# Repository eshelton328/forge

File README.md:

# forge

Hardware design monorepo for KiCad PCB projects with automated CI/CD.

Repository: [eshelton328/forge](https://github.com/eshelton328/forge).

For the alarm product, start with the [Rooster engineering map](projects/rooster/README.md).
Agent guidance is in [AGENTS.md](AGENTS.md). The [October 4 audit](docs/audits/2026-10-04-forge-rooster.md)
covers source consolidation, hardware readiness, costs and the development workflow.

## Repository Structure

```
forge/
├── Makefile          # make check / erc / drc / fab-drc
├── boards/           # Individual board projects
├── designs/          # Schematic studies before PCB layout
├── enclosures/       # Product packaging, Blender models and fit evidence
├── fab-rules/        # DRC rule templates per fab house
├── firmware/rooster/ # Reserved application, diagnostics and shared-code paths
├── kibot/            # KiBot output generation configs
├── libs/             # Shared libraries (symbols, footprints, 3D models)
├── projects/rooster/ # Product entry point and source manifest
├── releases/rooster/ # Release conventions; no product release declared
├── scripts/          # Automation scripts
├── emi/              # openEMS + gerber2ems (FDTD / EMI-adjacent smoke; see emi/README.md)
└── .github/workflows # CI/CD pipelines
```

## Boards

<!-- board-catalog-start -->
| Board | Description | Layers |
|---|---|---:|
| [alec-controls](boards/alec-controls/README.md) | ALEC bottom controls with three settings buttons and hardware enable switch | 2 |
| [alec-front](boards/alec-front/README.md) | ALEC exterior battery-check button and RGB LED | 2 |
| [alec-main](boards/alec-main/README.md) | ALEC main board with ESP32-S3, dual TPS63070 rails, audio and remote controls | 4 |
| [alec-sensor](boards/alec-sensor/README.md) | ALEC shower presence sensor prototype with ESP32-S3, RV-3028, isolated LD2410C and dual TPS63070 rails | 4 |
| [esp32s3-devkit](boards/esp32s3-devkit/README.md) | ESP32-S3-WROOM-1 development board with TPS63070 buck-boost and USB-C | 4 |
| [esp32s3-devkit-5v](boards/esp32s3-devkit-5v/README.md) | ESP32-S3-WROOM-1 dev board with dual TPS63070 rails (3.3V + 5V), USB-C | 4 |
| [tps63070-breakout](boards/tps63070-breakout/README.md) | TPS63070 3.3V buck-boost breakout board | 2 |
<!-- board-catalog-end -->

Each board README includes schematic previews, a downloadable schematic PDF, top/bottom 3D renders and a populated GLB model. The board catalog and these assets are updated automatically after merges to `main`.

The **ALEC** alarm uses `alec-main`, `alec-controls` and `alec-front` together. The main board carries the ESP32-S3, dual power converters and audio circuit; the two smaller boards carry the protected settings controls and exterior battery-check button/RGB LED. These are engineering prototypes with physical qualification pending. See the [full PCB and enclosure test report](boards/alec-main/review/TEST-REPORT.md).

The separate [ALEC Sensor](boards/alec-sensor/) is the shower presence companion: a routed four-layer PCB with LD2410C radar, RTC wake and isolated sensor signals. Its [S1 report](boards/alec-sensor/TEST-REPORT.md) covers electrical checks, free-tool power screening and nominal enclosure fit. Scheduled sensing is the proposed battery-saving default; waterproofing and wet detection still require prototypes.

## Enclosures

| Enclosure | Board | Status |
|---|---|---|
| [ALEC v4.2](enclosures/alec/pcb-revision/) | alec-main, alec-controls, alec-front | Integrated PCB prototype: 105 mm cube, four perforated walls, 1.3-inch OLED and three AA cells; physical tests pending |
| [ALEC Sensor S1.1](enclosures/alec-sensor/) | alec-sensor | Circular 116 mm × 54 mm fit prototype with rear-access cells/controls, actual PCB and LD2410C; RF, sealing and thermal tests pending |
| [ALEC v4.1 reference](enclosures/alec/) | esp32s3-devkit-5v | Earlier packaging reference with the bench board |

The enclosure project includes editable Blender scenes, inline preview images, dimensional sources, a parts register and a reproducible test report. Open its README to download the models and review the current fit limits.

## CI/CD Pipeline

Every pull request automatically runs:
- **PR title** must follow [Conventional Commits](https://www.conventionalcommits.org/) (e.g. `feat:`, `fix:`, `chore:`, `ci:`)
- **`pytest`** on `tests/` (Python **3.12**; see [`.github/workflows/pytest.yml`](.github/workflows/pytest.yml) — Spice integration cases skip unless `ngspice`/Docker exist)
- **Open-source EMS (openEMS + gerber2ems)** — optional path-filtered workflow ([`.github/workflows/emi-checks.yml`](.github/workflows/emi-checks.yml)): builds pinned **openEMS** + **gerber2ems** and runs an upstream example slice ([`emi/README.md`](emi/README.md)); not every PR
- **ERC** (Electrical Rules Check) on schematics
- **DRC** (Design Rules Check) against multiple fab house rules (JLCPCB, PCBWay)

The KiCad workflow always runs, but it only **executes** ERC/DRC for boards that are in scope: changes under `boards/<name>/` check only those boards, while changes to `libs/`, `fab-rules/`, `kibot/`, `scripts/`, the root `Makefile`, or `.github/workflows/pr-checks.yml` trigger checks on all boards. Doc-only diffs (e.g. just `README.md`) skip the heavy KiCad jobs to save time. **`pytest`** (see **`pytest.yml`**) runs on every PR regardless, so Python regressions cannot slip through doc-only merges.

The manually dispatched [fabrication workflow](.github/workflows/release.yml) generates files for a selected board; it does not currently run on release tags. Its outputs include:
- Fab-ready Gerber/drill ZIPs per fab house
- BOM and component placement files
- Schematic PDFs and board renders

These exports are not an approved Rooster manufacturing release. The product's
reviewed supplier packages and remaining assembly work are tracked separately;
see the [Rooster map](projects/rooster/README.md).

## Local Development

### Prerequisites

```bash
brew install --cask kicad    # KiCad 10 (includes kicad-cli)
pip install kibot kikit       # Automation tools
```

### Running checks locally

From the repository root, the **Makefile** is the usual entry point. **Each command checks one board** — the one named by `BOARD` (default: `esp32s3-devkit`). Nothing scans every board unless you ask for that explicitly.

```bash
make help           # list targets
make list-boards    # show board folder names you can pass as BOARD=...

# Default single board (esp32s3-devkit)
make check
make drc

# A different board — either form (folder and .kicad_* basename must match)
make drc BOARD=other-board
make drc other-board
make check other-board

# Optional: run make check for every board under boards/ (e.g. before a release)
make check-all
```

`kicad-cli` is picked up from your `PATH` if present; on macOS it falls back to
`/Applications/KiCad/KiCad.app/Contents/MacOS/kicad-cli`. Override with
`KICAD_CLI=/path/to/kicad-cli make check`.

### Python tests (pytest)

```bash
pip install -r requirements.txt
python3 -m pytest tests/
```

With **`ngspice`** and **Docker** available, `tests/test_spice_run_sim_integration.py` runs end-to-end Spice smoke; otherwise those cases are **skipped** (same as default CI for `pytest.yml`).

**SPICE / simulation (boards with `sim.yml`):** CI builds [`sim/docker/Dockerfile`](sim/docker/Dockerfile) — same KiCad digest as ERC/DRC plus pinned **ngspice** and the repo **`requirements.txt`** — and runs export + `run_sim.py` inside that image ([`sim/README.md`](sim/README.md)). Local parity: **`make sim-board-docker BOARD=tps63070-breakout`** or **`scripts/sim/run-spice-in-docker.sh --board …`**.

Raw commands (equivalent to the Makefile):

```bash
kicad-cli sch erc --exit-code-violations --format json -o boards/esp32s3-devkit/erc.json \
  boards/esp32s3-devkit/esp32s3-devkit.kicad_sch

kicad-cli pcb drc --exit-code-violations --refill-zones --schematic-parity --format json \
  -o boards/esp32s3-devkit/drc-default.json boards/esp32s3-devkit/esp32s3-devkit.kicad_pcb

./scripts/run-drc-all-fabs.sh boards/esp32s3-devkit
```

### Adding a new board

1. Create a new directory under `boards/`
2. Add a `board.yml` with layer count and fab targets
3. If using shared libraries, create project-local `fp-lib-table` / `sym-lib-table` pointing to `../../libs/`
4. Generate the initial schematic and model downloads with `bash scripts/ci/generate-board-images.sh boards/<name>` (`kicad-cli` must be on `PATH`), then run `python3 scripts/ci/update-board-readmes.py` to refresh the gallery and root catalog. Commit the generated `docs/` assets with the board.
5. Push a PR -- CI will automatically run checks; merge automation refreshes the galleries and catalog again.

## Fab House Rules

DRC rules for each fab house are stored in `fab-rules/` as `.kicad_dru` files. CI swaps these in and runs DRC to tell you which fabs your design is compatible with.

2-layer and 4-layer rules each come in two tiers where noted: **standard** (baseline process) vs **advanced** (tighter vias/clearances, typically higher cost). Each board declares which rule keys it runs in `board.yml`.

| Fab House | Rule File | Notes |
|-----------|-----------|-------|
| JLCPCB 2L Standard | `jlcpcb-2layer-standard.kicad_dru` | 0.3mm via drill, 0.15mm annular ring |
| JLCPCB 2L Advanced | `jlcpcb-2layer-advanced.kicad_dru` | 0.2mm via drill, 0.1mm annular ring |
| JLCPCB 4L Standard | `jlcpcb-4layer.kicad_dru` | |
| JLCPCB 4L Advanced | `jlcpcb-4layer-advanced.kicad_dru` | Tighter annular / hole clearance / pad-track clearance vs standard 4L |
| PCBWay 2L Standard | `pcbway-2layer-standard.kicad_dru` | 0.3mm via drill, 0.45mm via pad |
| PCBWay 2L Advanced | `pcbway-2layer-advanced.kicad_dru` | 0.2mm via drill, 0.35mm via pad |
| PCBWay 4L Standard | `pcbway-4layer.kicad_dru` | |
| PCBWay 4L Advanced | `pcbway-4layer-advanced.kicad_dru` | 0.2mm via drill, 0.35mm via pad vs standard 4L |

## Naming compatibility

The repository and checkout directory are named `forge`. The local and CI Docker
images use `forge-sim` and `forge-open-ems`.

A few references intentionally retain the previous name:

- The GitHub environment `the-forge` holds `FORGE_PAT`, used by the README publishing
  workflow. Keep the workflow attached to it until the secret is migrated.
- `scripts/alarm/design.py` uses `the-forge/alec/` as a deterministic UUID namespace.
  Changing it would regenerate KiCad component, pin and wire IDs.
- Recorded simulation reports, exported netlists and test transcripts retain the
  image names and paths used when they were produced. The physics report and its
  `scripts/physics/render_report.py` renderer retain their original GitHub link;
  the renderer is covered by the archived verification source hashes. Update these
  records through their normal regeneration and verification workflows.

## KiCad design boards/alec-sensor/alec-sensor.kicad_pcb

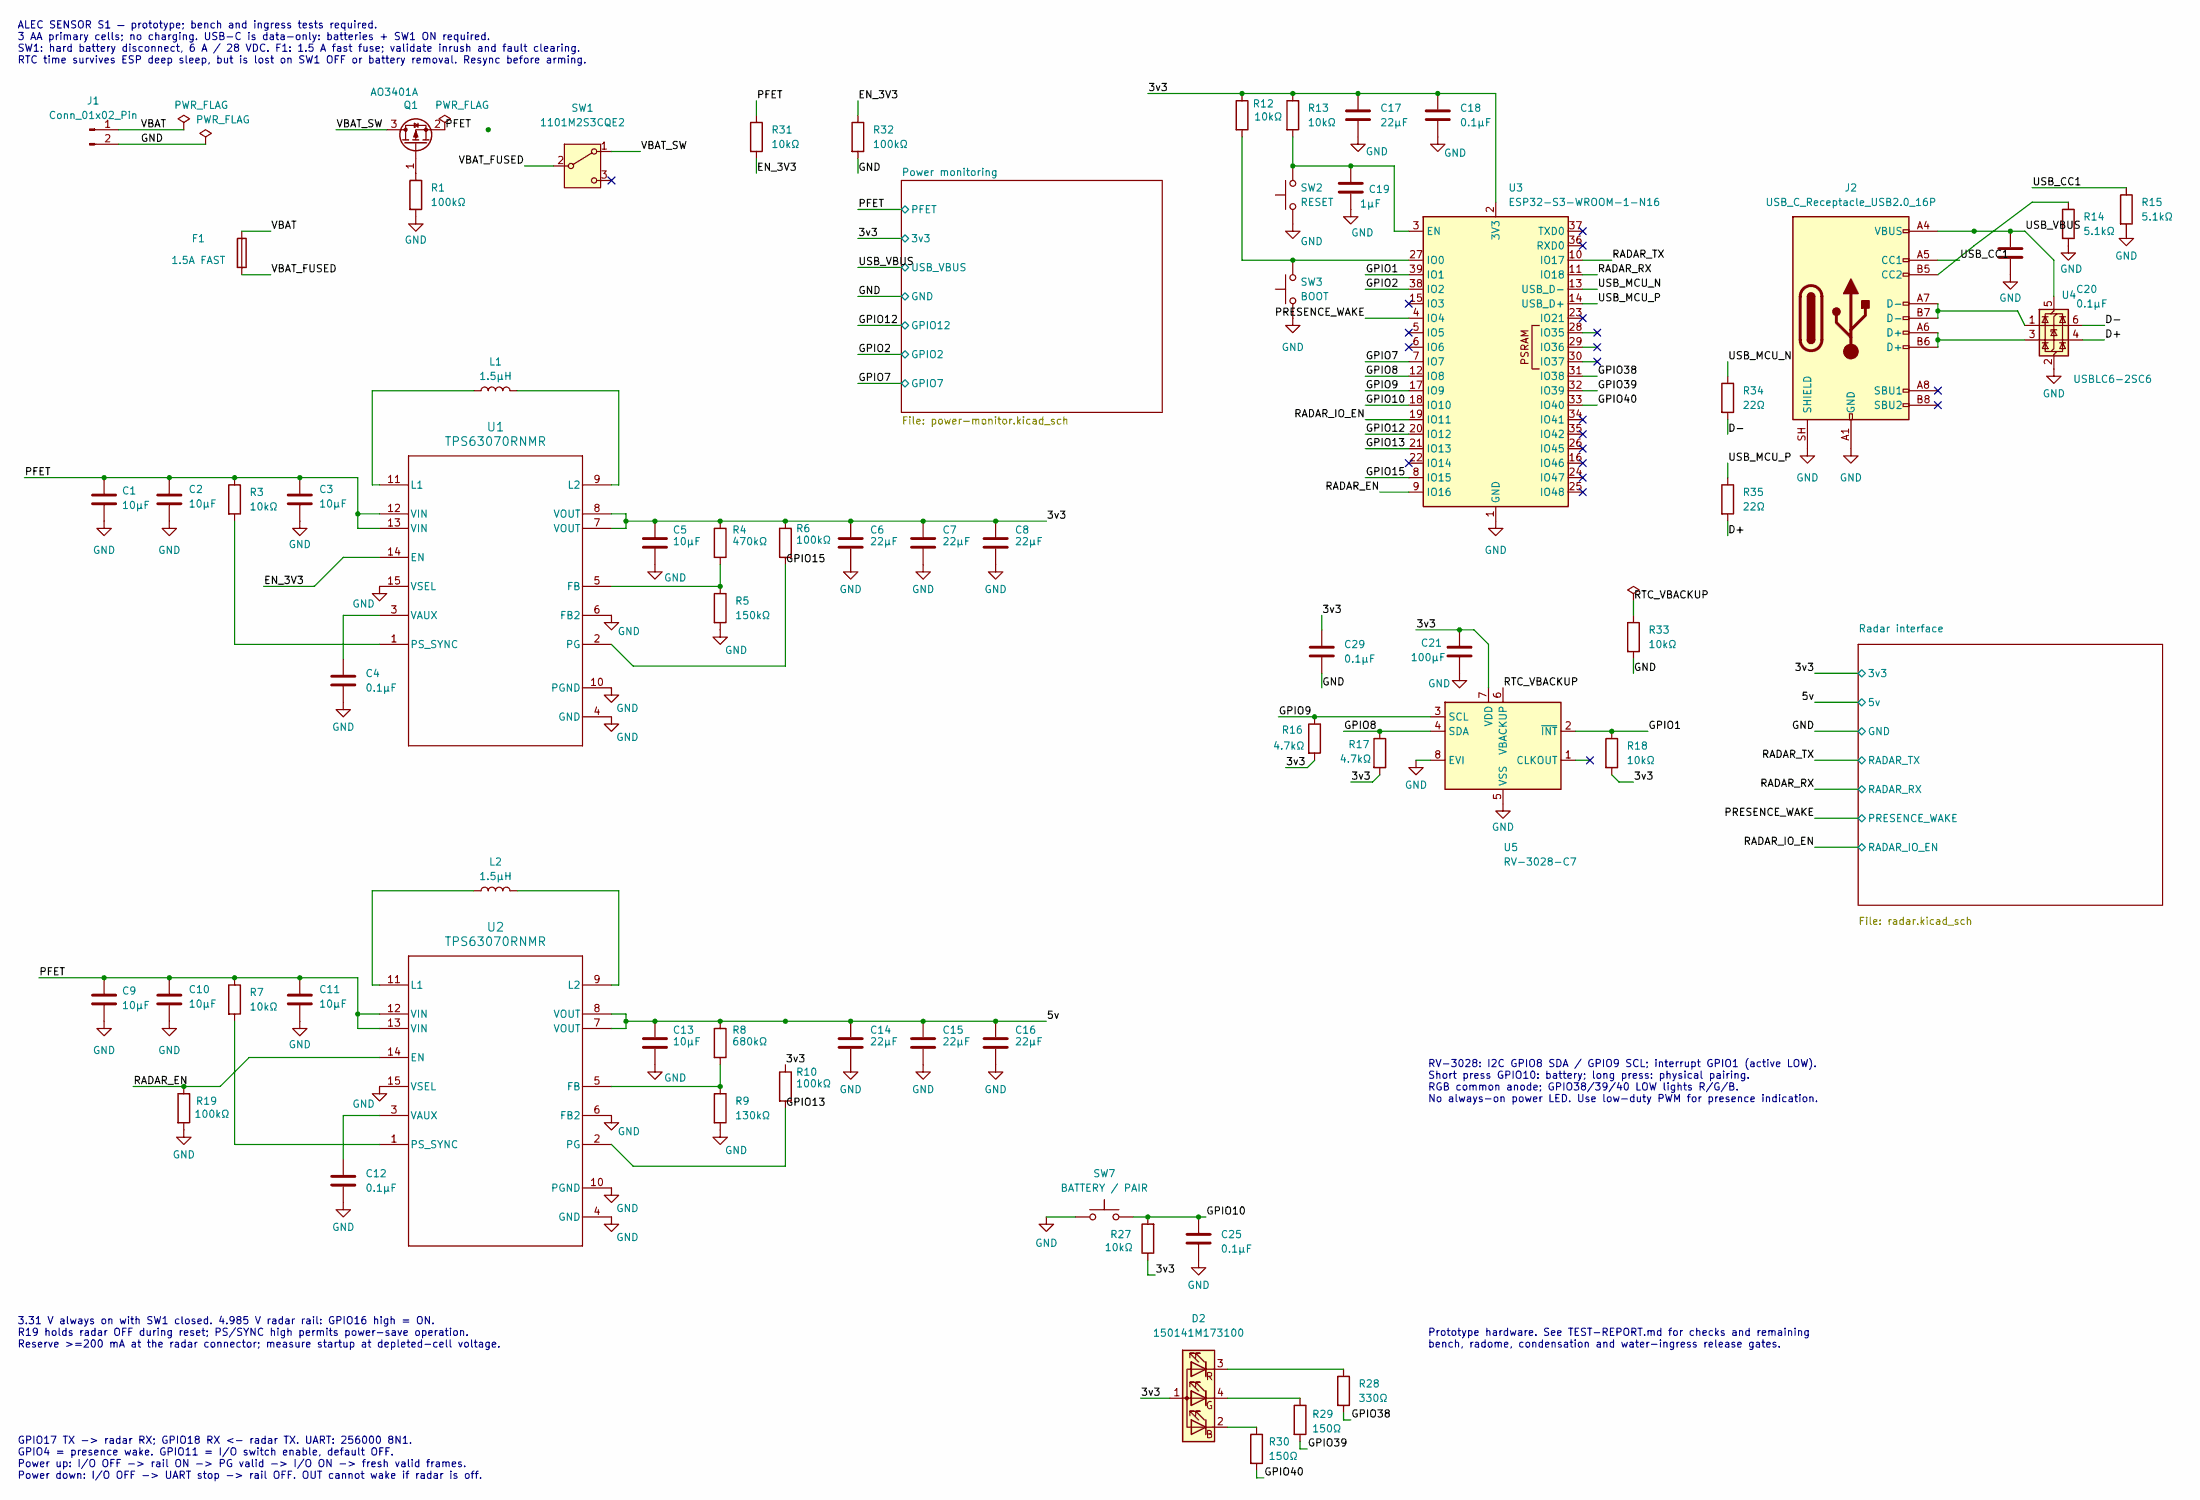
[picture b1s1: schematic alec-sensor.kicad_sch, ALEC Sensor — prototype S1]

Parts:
C1, C2, C9, C10: 10µF; C_0805_2012Metric; Voltage 25V; MPN GRM21BR61E106KA73L; LCSC# C84416
C3, C5, C11, C13: 10µF; C_0603_1608Metric; Voltage 10V; MPN GRT188R61A106KE13D; LCSC# C782172
C4, C12, C18, C20, C25, C29: 0.1µF; C_0402_1005Metric; Voltage 16V; MPN GRM155R71C104KA88D; LCSC# C71629
C6, C7, C8, C14, C15, C16: 22µF; C_1206_3216Metric; Voltage 16V; MPN GRM31CR61C226KE15L; LCSC# C77088
C17: 22µF; C_0805_2012Metric; Voltage 10V; MPN GRM21BR61A226ME44L; LCSC# C441864
C19: 1µF; C_0402_1005Metric; Voltage 10V; MPN GRM155R61A105KE15D; LCSC# C76999
C21: 100µF; C_1206_3216Metric; Voltage 6.3V; MPN CL31A107MQHNNNE; LCSC# C15008
D2: 150141M173100; LED_RGB_Wuerth-PLCC4_3.2x2.8mm_150141M173100; MPN 150141M173100; LCSC# C5342281
F1: 1.5A FAST; Fuse_0603_1608Metric; MPN 046701.5NRHF; LCSC# C187608
J1: Conn_01x02_Pin; JST_PH_B2B-PH-SM4-TB_1x02-1MP_P2.00mm_Vertical; MPN B2B-PH-SM4-TB(LF)(SN); LCSC# C160352
J2: USB_C_Receptacle_USB2.0_16P; USB_C_HRO_Overhang; MPN TYPE-C-31-M-12; LCSC# C165948
L1, L2: 1.5µH; IND_XFL4020-152MEC; MPN XFL4020-152MEC; LCSC# C3033018
Q1: AO3401A; SOT-23; MPN AO3401A; LCSC# C15127
R1, R6, R10, R19, R32: 100kΩ; R_0402_1005Metric; MPN RC0402FR-07100KL; LCSC# C60491
R3, R7, R12, R13, R18, R27, R31, R33: 10kΩ; R_0402_1005Metric; MPN RC0402FR-0710KL; LCSC# C60490
R4: 470kΩ; R_0402_1005Metric; Tolerance 1%; MPN RC0402FR-07470KL; LCSC# C137976
R5: 150kΩ; R_0402_1005Metric; Tolerance 1%; MPN RC0402FR-07150KL; LCSC# C93947
R8: 680kΩ; R_0402_1005Metric; Tolerance 1%; MPN RC0402FR-07680KL; LCSC# C163456
R9: 130kΩ; R_0402_1005Metric; Tolerance 1%; MPN RC0402FR-07130KL; LCSC# C93946
R14, R15: 5.1kΩ; R_0402_1005Metric; Tolerance 1%; MPN RC0402FR-075K1L; LCSC# C105872
R16, R17: 4.7kΩ; R_0402_1005Metric; MPN RC0402FR-074K7L; LCSC# C105871
R28: 330Ω; R_0402_1005Metric; MPN RC0402FR-07330RL; LCSC# C105875
R29, R30: 150Ω; R_0402_1005Metric; MPN 0402WGF1500TCE; LCSC# C25082
R34, R35: 22Ω; R_0402_1005Metric; MPN RC0402FR-0722RL; LCSC# C114765
SW1: 1101M2S3CQE2; SW_CK_1101M2S3CQE2; MPN 1101M2S3CQE2; LCSC# C221538
SW2: RESET; SW_Push_1P1T_XKB_TS-1187A; MPN TS-1187A-B-A-B; LCSC# C318884
SW3: BOOT; SW_Push_1P1T_XKB_TS-1187A; MPN TS-1187A-B-A-B; LCSC# C318884
SW7: BATTERY / PAIR; SW_Push_1P1T_XKB_TS-1187A; MPN TS-1187A-B-A-B; LCSC# C318884
U1, U2: TPS63070RNMR; TPS63070; MPN TPS63070RNMR; LCSC# C109322
U3: ESP32-S3-WROOM-1-N16; ESP32-S3-WROOM-1_Overhang; MPN ESP32-S3-WROOM-1-N16; LCSC# C2913199
U4: USBLC6-2SC6; SOT-23-6; MPN USBLC6-2SC6; LCSC# C7519
U5: RV-3028-C7; MicroCrystal_C7_SON-8_1.5x3.2mm_P0.9mm; MPN RV-3028-C7-32.768kHz-1ppm-TA-QC; LCSC# C3019759

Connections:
/3v3: C5.1, C6.1, C7.1, C8.1, C17.1, C18.1, C21.1, C29.1, D2.1 (A), R4.1, R6.1, R10.1, R12.1, R13.1, R16.2, R17.2, R18.2, R27.1, U1.7 (VOUT), U1.8 (VOUT), U3.2 (3V3), U5.7 (VDD); also elsewhere on the board
/5v: C13.1, C14.1, C15.1, C16.1, R8.1, U2.7 (VOUT), U2.8 (VOUT); also elsewhere on the board
/D+: R35.2, U4.4 (I/O2)
/D-: R34.2, U4.6 (I/O1)
/EN_3V3: R31.2, R32.1, U1.14 (EN); also elsewhere on the board
/GPIO1: R18.1, U3.39 (IO1), U5.2 (~INT)
/GPIO2: U3.38 (IO2); also elsewhere on the board
/GPIO7: U3.7 (IO7); also elsewhere on the board
/GPIO8: R17.1, U3.12 (IO8), U5.4 (SDA)
/GPIO9: R16.1, U3.17 (IO9), U5.3 (SCL)
/GPIO10: C25.1, R27.2, SW7.2, U3.18 (IO10)
/GPIO12: U3.20 (IO12); also elsewhere on the board
/GPIO13: R10.2, U2.2 (PG), U3.21 (IO13); also elsewhere on the board
/GPIO15: R6.2, U1.2 (PG), U3.8 (IO15); also elsewhere on the board
/GPIO38: R28.2, U3.31 (IO38)
/GPIO39: R29.2, U3.32 (IO39)
/GPIO40: R30.2, U3.33 (IO40)
/PFET: C1.1, C2.1, C3.1, C9.1, C10.1, C11.1, Q1.2 (S), R3.1, R7.1, R31.1, U1.12 (VIN), U1.13 (VIN), U2.12 (VIN), U2.13 (VIN); also elsewhere on the board
/PRESENCE_WAKE: U3.4 (IO4); also elsewhere on the board
/RADAR_EN: R19.1, U2.14 (EN), U3.9 (IO16); also elsewhere on the board
/RADAR_IO_EN: U3.19 (IO11); also elsewhere on the board
/RADAR_RX: U3.11 (IO18); also elsewhere on the board
/RADAR_TX: U3.10 (IO17); also elsewhere on the board
/RTC_VBACKUP: R33.1, U5.6 (VBACKUP)
/USB_CC1: J2.A5 (CC1), R15.1
/USB_MCU_N: R34.1, U3.13 (USB_D-)
/USB_MCU_P: R35.1, U3.14 (USB_D+)
/USB_VBUS: C20.1, J2.A4 (VBUS), J2.A9 (VBUS), J2.B4 (VBUS), J2.B9 (VBUS), U4.5 (VBUS); also elsewhere on the board
/VBAT: F1.1, J1.1
/VBAT_FUSED: F1.2, SW1.2 (B)
/VBAT_SW: Q1.3 (D), SW1.1 (A)
GND: C1.2, C2.2, C3.2, C4.2, C5.2, C6.2, C7.2, C8.2, C9.2, C10.2, C11.2, C12.2, C13.2, C14.2, C15.2, C16.2, C17.2, C18.2, C19.2, C20.2, C21.2, C25.2, C29.2, J1.2, J2.A1 (GND), J2.A12 (GND), J2.B1 (GND), J2.B12 (GND), J2.SH (SHIELD), R1.2, R5.2, R9.2, R14.2, R15.2, R19.2, R32.2, R33.2, SW2.1, SW3.1, SW7.1, U1.4 (GND), U1.6 (FB2), U1.10 (PGND), U1.15 (VSEL), U2.4 (GND), U2.6 (FB2), U2.10 (PGND), U2.15 (VSEL), U3.1 (GND), U3.40 (GND), U3.41 (GND), U4.2 (GND), U5.5 (VSS), U5.8 (EVI); also elsewhere on the board
unnamed: D2.2 (BK), R30.1
unnamed: D2.4 (GK), R29.1
unnamed: D2.3 (RK), R28.1
unnamed: J2.B5 (CC2), R14.1
unnamed: J2.A6 (D+), J2.B6 (D+), U4.3 (I/O2)
unnamed: J2.A7 (D-), J2.B7 (D-), U4.1 (I/O1)
unnamed: Q1.1 (G), R1.1
unnamed: R4.2, R5.1, U1.5 (FB)
unnamed: L1.1, U1.11 (L1)
unnamed: L1.2, U1.9 (L2)
unnamed: R3.2, U1.1 (PS_SYNC)
unnamed: C4.1, U1.3 (VAUX)
unnamed: R8.2, R9.1, U2.5 (FB)
unnamed: L2.1, U2.11 (L1)
unnamed: L2.2, U2.9 (L2)
unnamed: R7.2, U2.1 (PS_SYNC)
unnamed: C12.1, U2.3 (VAUX)
unnamed: C19.1, R13.2, SW2.2, U3.3 (EN)
unnamed: R12.2, SW3.2, U3.27 (IO0)

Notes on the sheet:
ALEC SENSOR S1 — prototype; bench and ingress tests required. 3 AA primary cells; no charging. USB-C is data-only: batteries + SW1 ON required. SW1: hard battery disconnect, 6 A / 28 VDC. F1: 1.5 A fast fuse; validate inrush and fault clearing. RTC time survives ESP deep sleep, but is lost on SW1 O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
3.31 V always on with SW1 closed. 4.985 V radar rail: GPIO16 high = ON. R19 holds radar OFF during reset; PS/SYNC high permits power-save operation. Reserve >=200 mA at the radar connector; measure startup at depleted-cell voltage.
GPIO17 TX -> radar RX; GPIO18 RX <- radar TX. UART: 256000 8N1. GPIO4 = presence wake. GPIO11 = I/O switch enable, default OFF. Power up: I/O OFF -> rail ON -> PG valid -> I/O ON -> fresh valid frames. Power down: I/O OFF -> UART stop -> rail OFF. OUT cannot wake if radar is off.
RV-3028: I2C GPIO8 SDA / GPIO9 SCL; interrupt GPIO1 (active LOW). Short press GPIO10: battery; long press: physical pairing. RGB common anode; GPIO38/39/40 LOW lights R/G/B. No always-on power LED. Use low-duty PWM for presence indication.
Prototype hardware. See TEST-REPORT.md for checks and remaining bench, radome, condensation and water-ingress release gates.

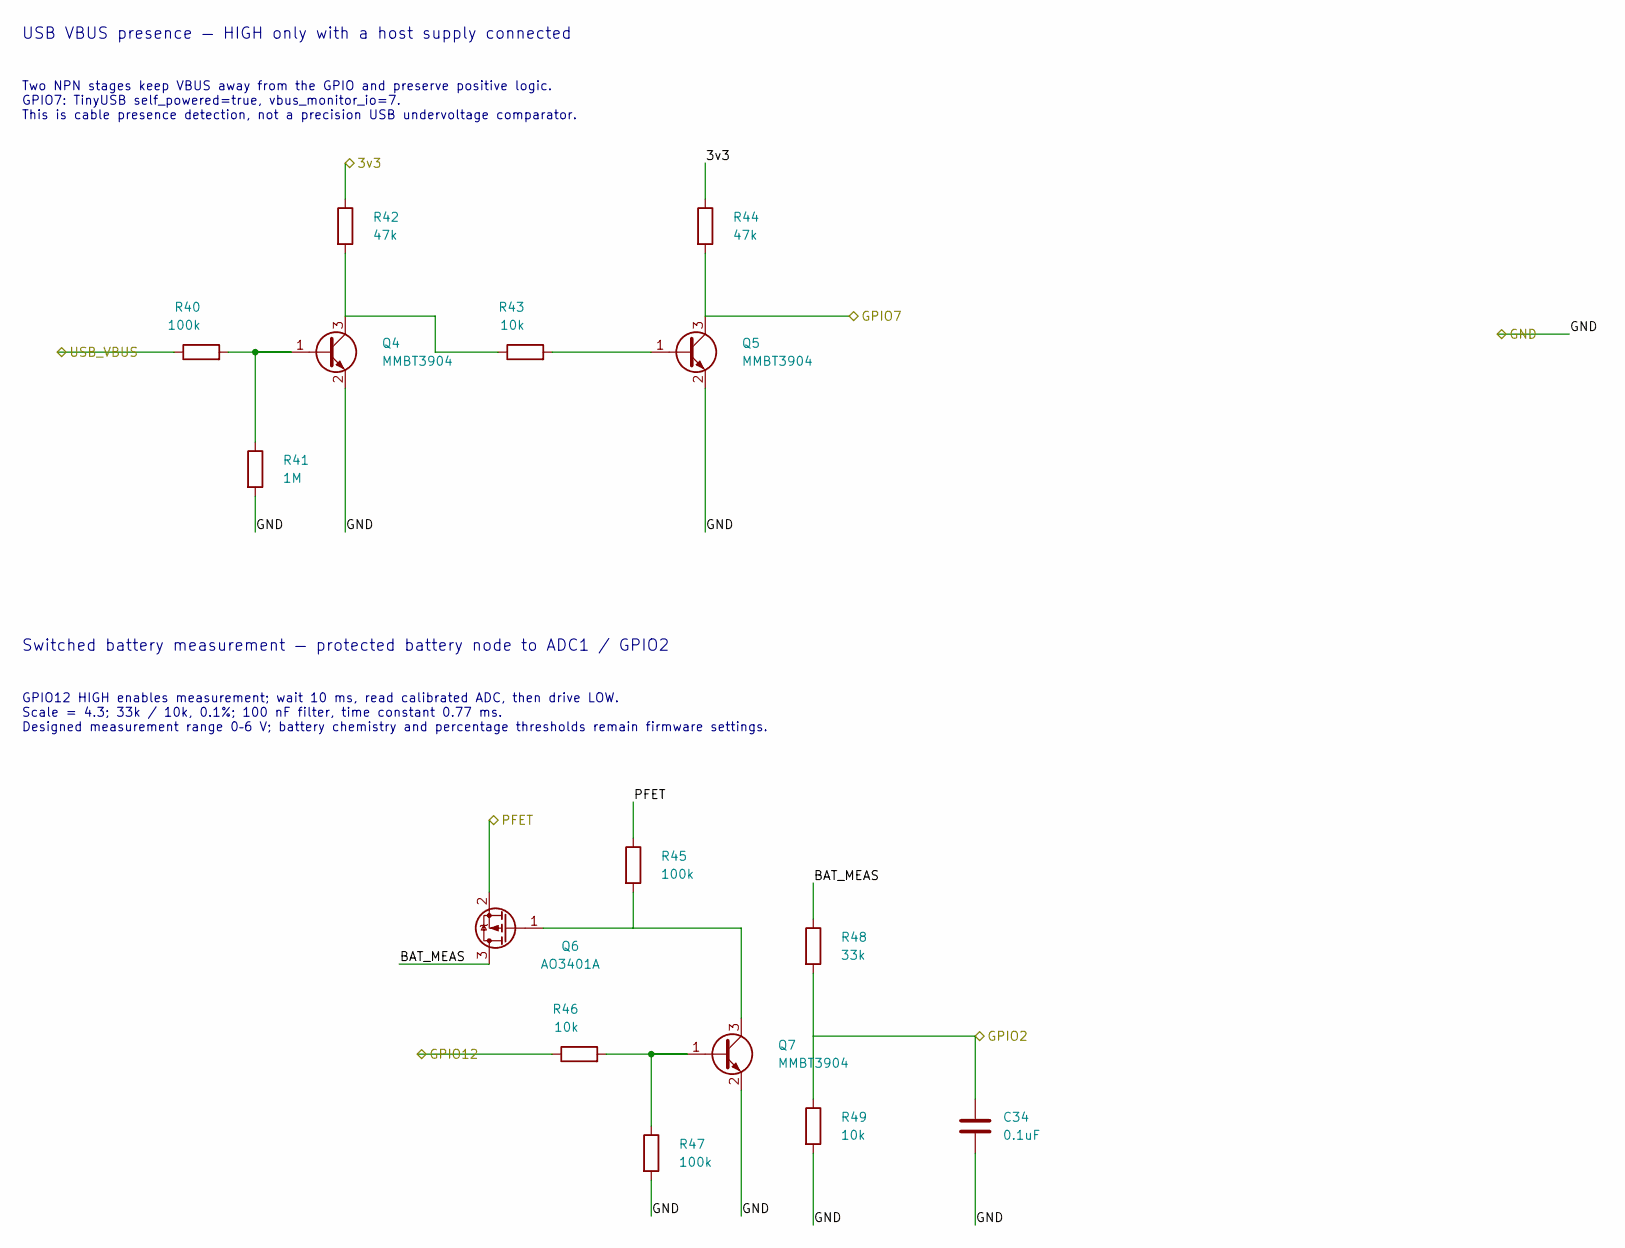
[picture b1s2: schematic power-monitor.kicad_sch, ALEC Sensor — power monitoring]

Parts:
C34: 0.1uF; C_0402_1005Metric; Voltage 16V; MPN GRM155R71C104KA88D; LCSC# C71629
Q4, Q5, Q7: MMBT3904; SOT-23; MPN MMBT3904LT1G; LCSC# C81464
Q6: AO3401A; SOT-23; MPN AO3401A; LCSC# C15127
R40, R45, R47: 100k; R_0402_1005Metric; MPN RC0402FR-07100KL; LCSC# C60491
R41: 1M; R_0402_1005Metric; MPN RC0402FR-071ML; LCSC# C138033
R42, R44: 47k; R_0402_1005Metric; MPN RC0402FR-0747KL; LCSC# C93943
R43, R46: 10k; R_0402_1005Metric; MPN RC0402FR-0710KL; LCSC# C60490
R48: 33k; R_0402_1005Metric; Tolerance 0.1%; MPN RT0402BRD0733KL; LCSC# C728559
R49: 10k; R_0402_1005Metric; Tolerance 0.1%; MPN RT0402BRD0710KL; LCSC# C190095

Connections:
/3v3: R42.1, R44.1; also elsewhere on the board
/GPIO2: C34.1, R48.2, R49.1; also elsewhere on the board
/GPIO7: Q5.3 (C), R44.2; also elsewhere on the board
/GPIO12: R46.1; also elsewhere on the board
/PFET: Q6.2 (S), R45.1; also elsewhere on the board
/Power monitoring/BAT_MEAS: Q6.3 (D), R48.1
/USB_VBUS: R40.1; also elsewhere on the board
GND: C34.2, Q4.2 (E), Q5.2 (E), Q7.2 (E), R41.2, R47.2, R49.2; also elsewhere on the board
unnamed: Q4.1 (B), R40.2, R41.1
unnamed: Q4.3 (C), R42.2, R43.1
unnamed: Q5.1 (B), R43.2
unnamed: Q6.1 (G), Q7.3 (C), R45.2
unnamed: Q7.1 (B), R46.2, R47.1

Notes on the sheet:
USB VBUS presence — HIGH only with a host supply connected
Two NPN stages keep VBUS away from the GPIO and preserve positive logic. GPIO7: TinyUSB self_powered=true, vbus_monitor_io=7. This is cable presence detection, not a precision USB undervoltage comparator.
Switched battery measurement — protected battery node to ADC1 / GPIO2
GPIO12 HIGH enables measurement; wait 10 ms, read calibrated ADC, then drive LOW. Scale = 4.3; 33k / 10k, 0.1%; 100 nF filter, time constant 0.77 ms. Designed measurement range 0–6 V; battery chemistry and percentage thresholds remain firmware settings.

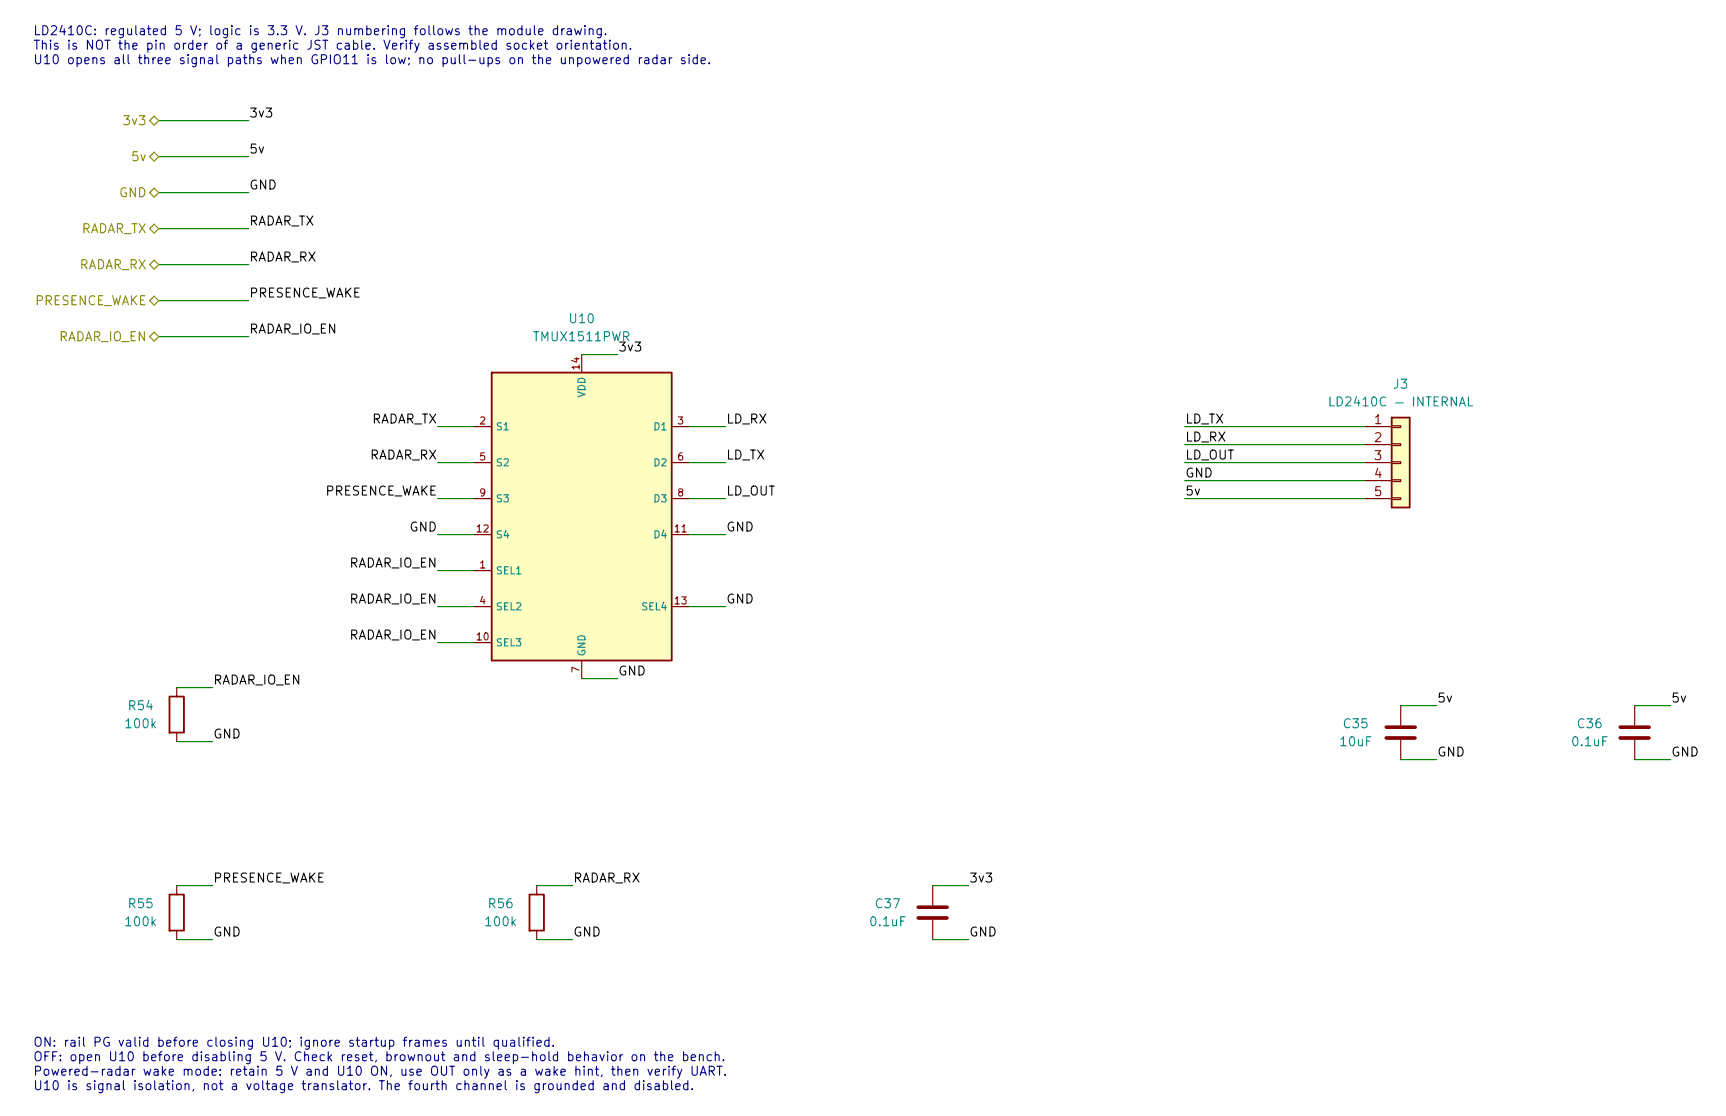
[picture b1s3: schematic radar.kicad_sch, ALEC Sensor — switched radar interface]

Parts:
C35: 10uF; C_0603_1608Metric; Voltage 10V; MPN GRT188R61A106KE13D; LCSC# C782172
C36, C37: 0.1uF; C_0603_1608Metric; Voltage 16V; MPN GRM188R71C104KA01D; LCSC# C45000
J3: LD2410C — INTERNAL; Samtec_SSW-105-01-F-S; MPN SSW-105-01-F-S; LCSC# C5930350
R54, R55, R56: 100k; R_0402_1005Metric; MPN RC0402FR-07100KL; LCSC# C60491
U10: TMUX1511PWR; TSSOP-14_4.4x5mm_P0.65mm; MPN TMUX1511PWR; LCSC# C2866750

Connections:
/3v3: C37.1, U10.14 (VDD); also elsewhere on the board
/5v: C35.1, C36.1, J3.5; also elsewhere on the board
/PRESENCE_WAKE: R55.1, U10.9 (S3); also elsewhere on the board
/RADAR_IO_EN: R54.1, U10.1 (SEL1), U10.4 (SEL2), U10.10 (SEL3); also elsewhere on the board
/RADAR_RX: R56.1, U10.5 (S2); also elsewhere on the board
/RADAR_TX: U10.2 (S1); also elsewhere on the board
/Radar interface/LD_OUT: J3.3, U10.8 (D3)
/Radar interface/LD_RX: J3.2, U10.3 (D1)
/Radar interface/LD_TX: J3.1, U10.6 (D2)
GND: C35.2, C36.2, C37.2, J3.4, R54.2, R55.2, R56.2, U10.7 (GND), U10.11 (D4), U10.12 (S4), U10.13 (SEL4); also elsewhere on the board

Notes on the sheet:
LD2410C: regulated 5 V; logic is 3.3 V. J3 numbering follows the module drawing. This is NOT the pin order of a generic JST cable. Verify assembled socket orientation. U10 opens all three signal paths when GPIO11 is low; no pull-ups on the unpowered radar side.
ON: rail PG valid before closing U10; ignore startup frames until qualified. OFF: open U10 before disabling 5 V. Check reset, brownout and sleep-hold behavior on the bench. Powered-radar wake mode: retain 5 V and U10 ON, use OUT only as a wake hint, then verify UART. U10 is signal isolation, not a 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
